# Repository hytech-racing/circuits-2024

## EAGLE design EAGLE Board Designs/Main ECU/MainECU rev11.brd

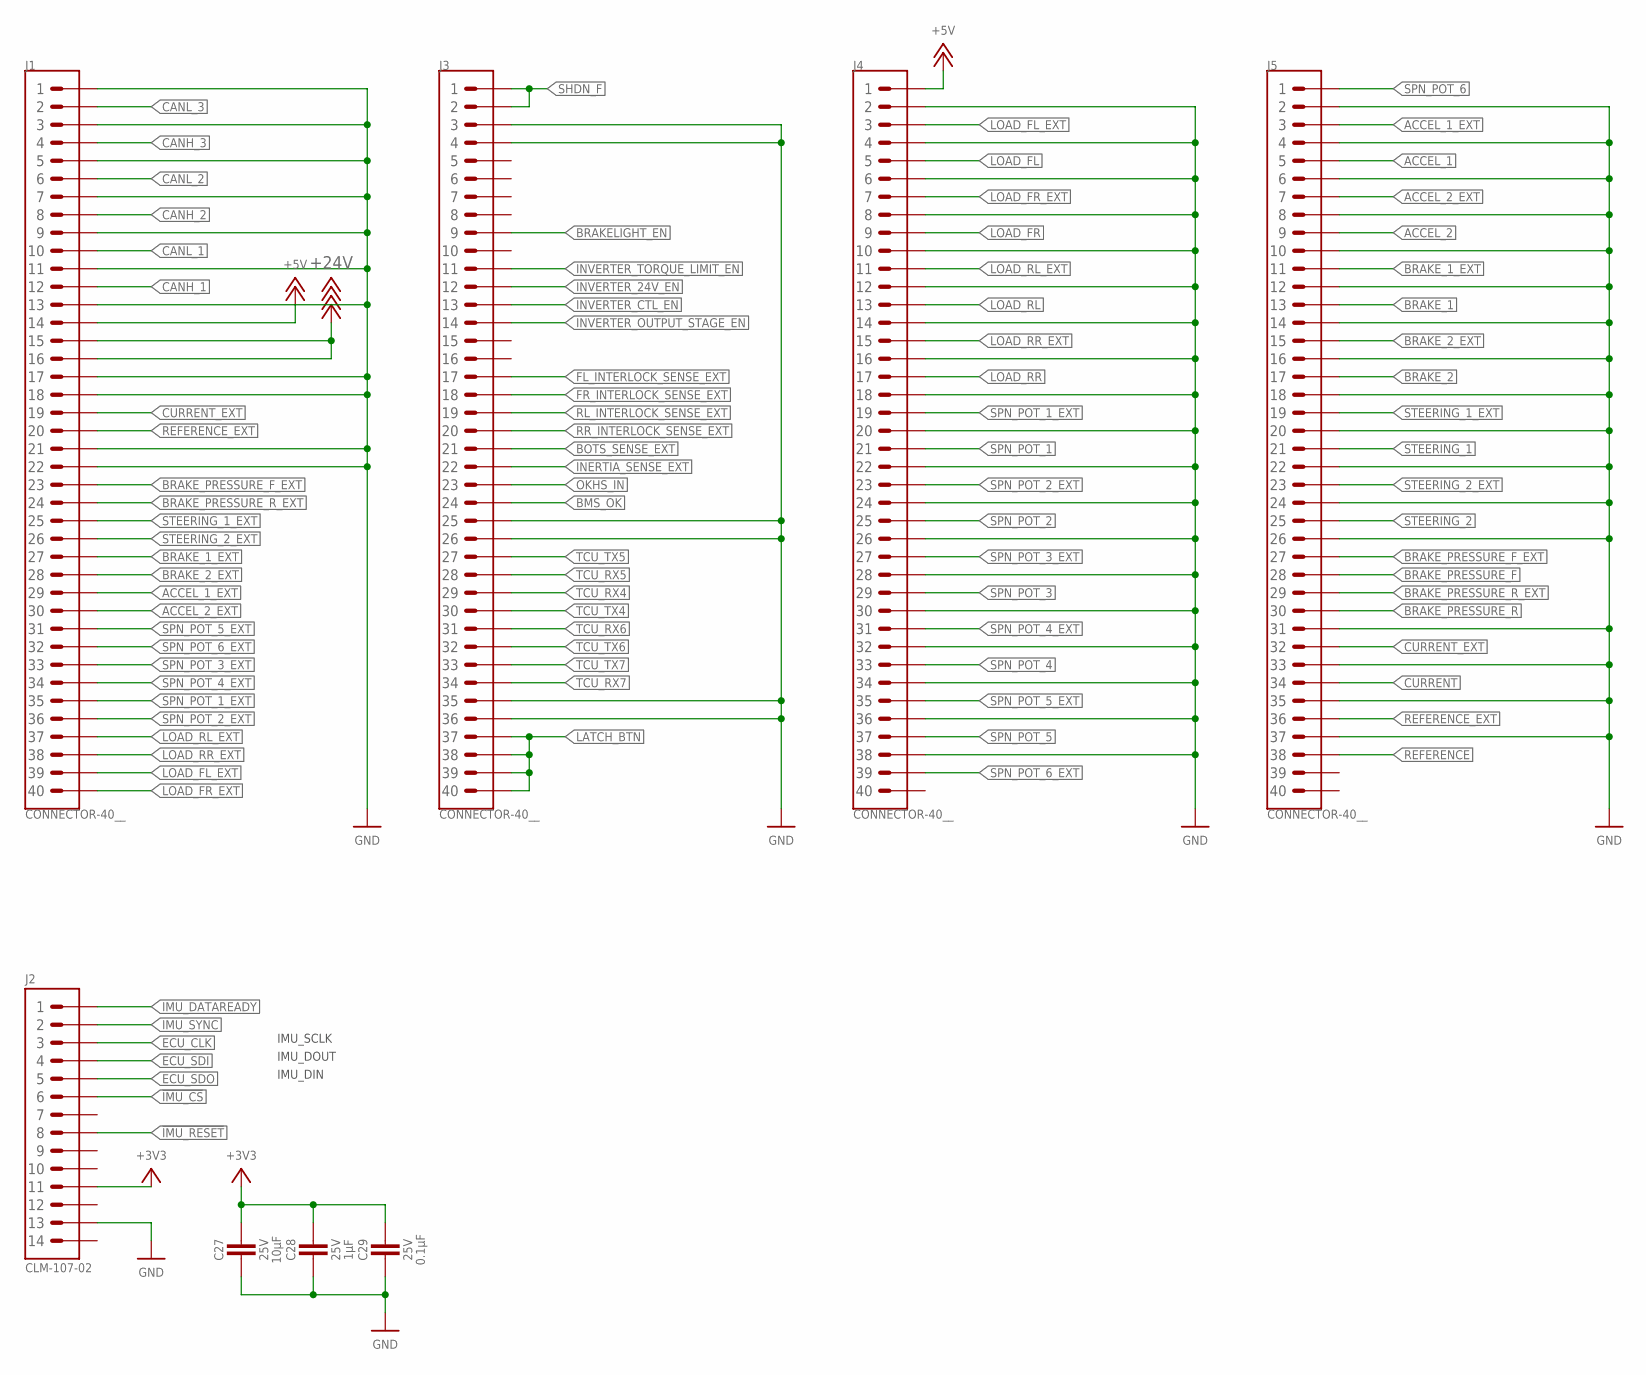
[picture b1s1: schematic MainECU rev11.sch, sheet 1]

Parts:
C27: CAPACITOR_0603_25V_10UF; 0603-CAP
C28: CAPACITOR_0603_25V_1UF; 0603-CAP
C29: CAPACITOR_0603_25V_0.1UF; 0603-CAP
J1, J3, J4, J5: CONNECTOR-40__; EHT-120-01
J2: ADIS16460

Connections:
!IMU_CS: J2.6; also elsewhere on the board
!IMU_RESET: J2.8; also elsewhere on the board
+3V3: C27.1, C28.1, C29.1, J2.11; also elsewhere on the board
+5V: J1.14, J4.1; also elsewhere on the board
+24V: J1.15, J1.16; also elsewhere on the board
ACCEL_1: J5.5; also elsewhere on the board
ACCEL_1_EXT: J1.29, J5.3
ACCEL_2: J5.9; also elsewhere on the board
ACCEL_2_EXT: J1.30, J5.7
BMS_OK: J3.24; also elsewhere on the board
BOTS_SENSE_EXT: J3.21; also elsewhere on the board
BRAKELIGHT_EN: J3.9; also elsewhere on the board
BRAKE_1: J5.13; also elsewhere on the board
BRAKE_1_EXT: J1.27, J5.11
BRAKE_2: J5.17; also elsewhere on the board
BRAKE_2_EXT: J1.28, J5.15
BRAKE_PRESSURE_F: J5.28; also elsewhere on the board
BRAKE_PRESSURE_F_EXT: J1.23, J5.27
BRAKE_PRESSURE_R: J5.30; also elsewhere on the board
BRAKE_PRESSURE_R_EXT: J1.24, J5.29
CANH_1: J1.12; also elsewhere on the board
CANH_2: J1.8; also elsewhere on the board
CANH_3: J1.4; also elsewhere on the board
CANL_1: J1.10; also elsewhere on the board
CANL_2: J1.6; also elsewhere on the board
CANL_3: J1.2; also elsewhere on the board
CURRENT: J5.34; also elsewhere on the board
CURRENT_EXT: J1.19, J5.32
ECU_CLK: J2.3; also elsewhere on the board
ECU_SDI: J2.4; also elsewhere on the board
ECU_SDO: J2.5; also elsewhere on the board
FL_INTERLOCK_SENSE_EXT: J3.17; also elsewhere on the board
FR_INTERLOCK_SENSE_EXT: J3.18; also elsewhere on the board
GND: C27.2, C28.2, C29.2, J1.1, J1.3, J1.5, J1.7, J1.9, J1.11, J1.13, J1.17, J1.18, J1.21, J1.22, J2.13, J3.3, J3.4, J3.25, J3.26, J3.35, J3.36, J4.2, J4.4, J4.6, J4.8, J4.10, J4.12, J4.14, J4.16, J4.18, J4.20, J4.22, J4.24, J4.26, J4.28, J4.30, J4.32, J4.34, J4.36, J4.38, J5.2, J5.4, J5.6, J5.8, J5.10, J5.12, J5.14, J5.16, J5.18, J5.20, J5.22, J5.24, J5.26, J5.31, J5.33, J5.35, J5.37; also elsewhere on the board
IMU_DATAREADY: J2.1; also elsewhere on the board
IMU_SYNC: J2.2; also elsewhere on the board
INERTIA_SENSE_EXT: J3.22; also elsewhere on the board
INVERTER_24V_EN: J3.12; also elsewhere on the board
INVERTER_CTL_EN: J3.13; also elsewhere on the board
INVERTER_OUTPUT_STAGE_EN: J3.14; also elsewhere on the board
INVERTER_TORQUE_LIMIT_EN: J3.11; also elsewhere on the board
LATCH_BTN: J3.37, J3.38, J3.39, J3.40; also elsewhere on the board
LOAD_FL: J4.5; also elsewhere on the board
LOAD_FL_EXT: J1.39, J4.3
LOAD_FR: J4.9; also elsewhere on the board
LOAD_FR_EXT: J1.40, J4.7
LOAD_RL: J4.13; also elsewhere on the board
LOAD_RL_EXT: J1.37, J4.11
LOAD_RR: J4.17; also elsewhere on the board
LOAD_RR_EXT: J1.38, J4.15
OKHS_IN: J3.23; also elsewhere on the board
REFERENCE: J5.38; also elsewhere on the board
REFERENCE_EXT: J1.20, J5.36
RL_INTERLOCK_SENSE_EXT: J3.19; also elsewhere on the board
RR_INTERLOCK_SENSE_EXT: J3.20; also elsewhere on the board
SHDN_F: J3.1, J3.2; also elsewhere on the board
SPN_POT_1: J4.21; also elsewhere on the board
SPN_POT_1_EXT: J1.35, J4.19
SPN_POT_2: J4.25; also elsewhere on the board
SPN_POT_2_EXT: J1.36, J4.23
SPN_POT_3: J4.29; also elsewhere on the board
SPN_POT_3_EXT: J1.33, J4.27
SPN_POT_4: J4.33; also elsewhere on the board
SPN_POT_4_EXT: J1.34, J4.31
SPN_POT_5: J4.37; also elsewhere on the board
SPN_POT_5_EXT: J1.31, J4.35
SPN_POT_6: J5.1; also elsewhere on the board
SPN_POT_6_EXT: J1.32, J4.39
STEERING_1: J5.21; also elsewhere on the board
STEERING_1_EXT: J1.25, J5.19
STEERING_2: J5.25; also elsewhere on the board
STEERING_2_EXT: J1.26, J5.23
TCU_RX4: J3.29; also elsewhere on the board
TCU_RX5: J3.28; also elsewhere on the board
TCU_RX6: J3.31; also elsewhere on the board
TCU_RX7: J3.34; also elsewhere on the board
TCU_TX4: J3.30; also elsewhere on the board
TCU_TX5: J3.27; also elsewhere on the board
TCU_TX6: J3.32; also elsewhere on the board
TCU_TX7: J3.33; also elsewhere on the board

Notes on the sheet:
IMU_DOUT
IMU_SCLK
IMU_DIN

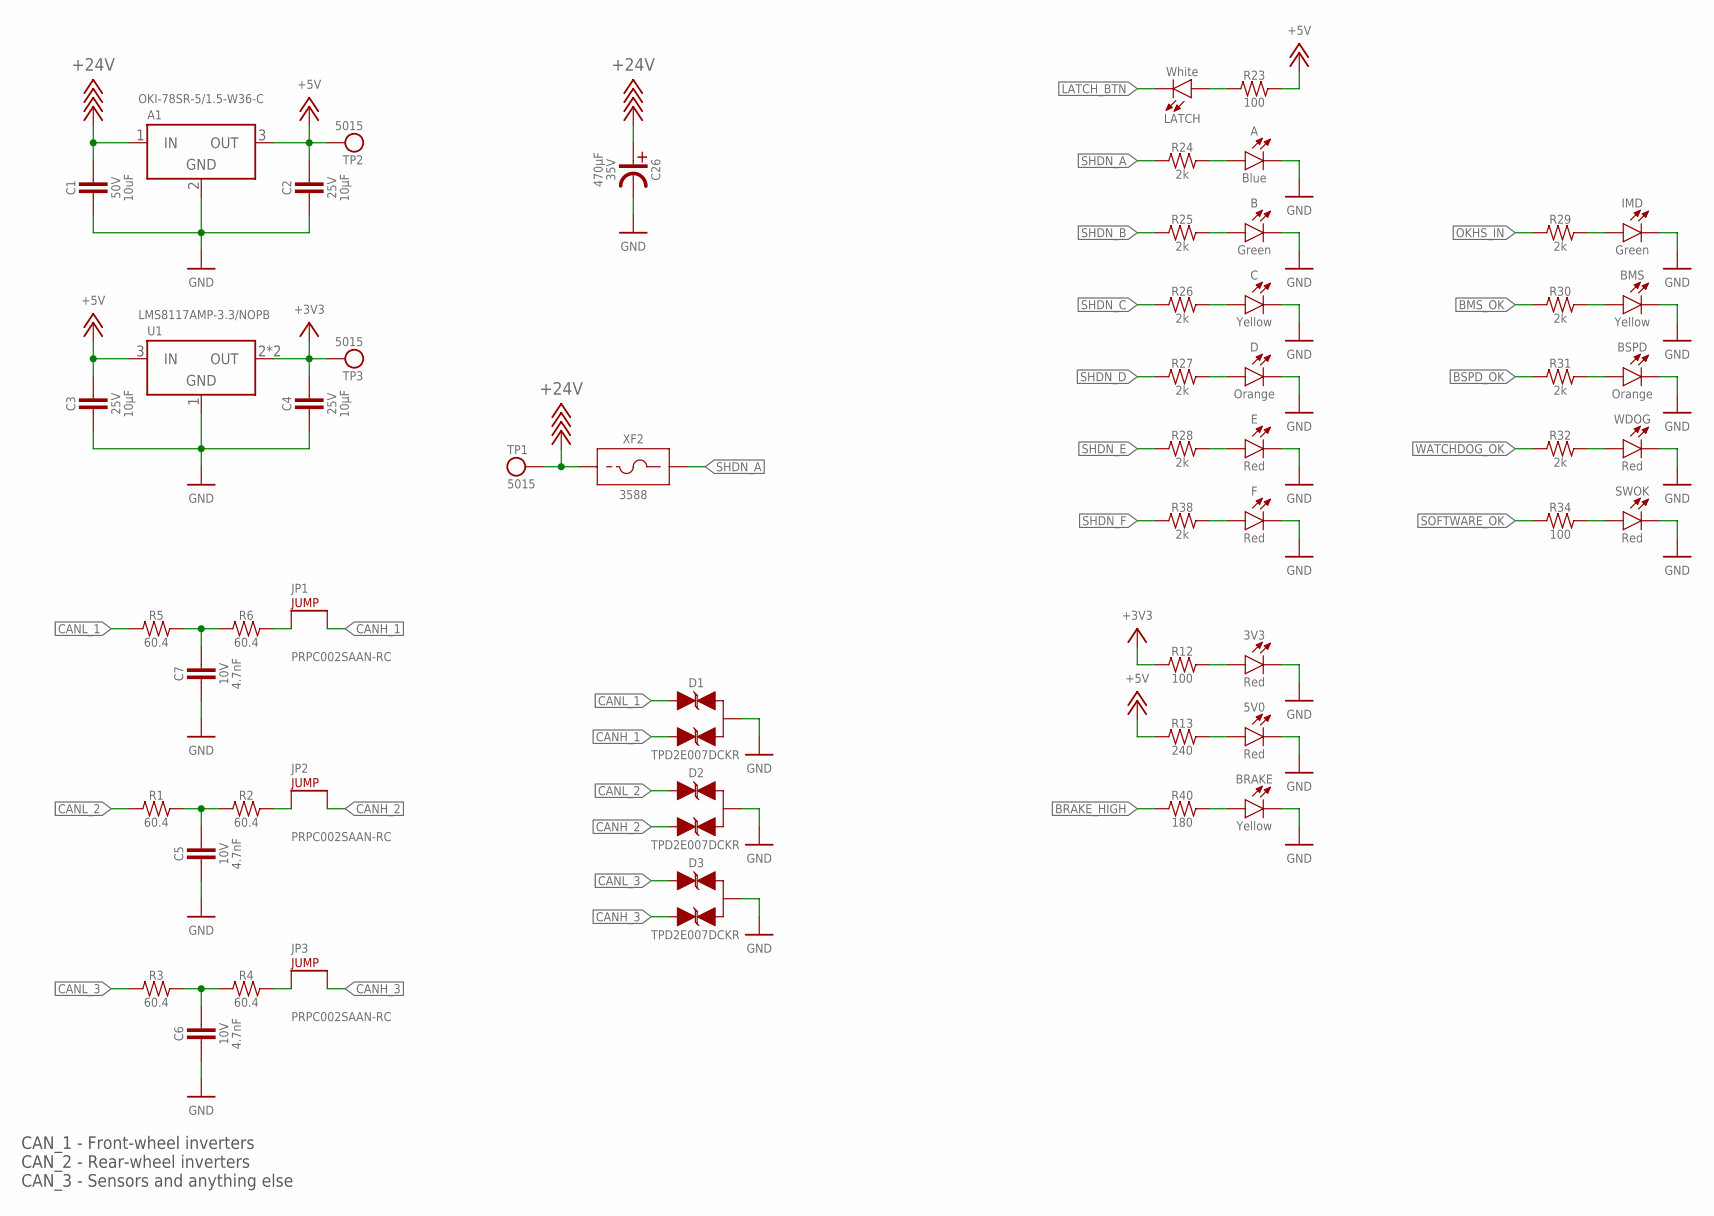
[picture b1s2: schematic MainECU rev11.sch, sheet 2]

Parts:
3V3, 5V0: LED_0603_RED; 0603-LED
A: LED_0603_BLUE; 0603-LED
A1: VOLTAGE_REGULATOR_MODULE_OKI-78SR_5V; OKI-78SR
B: LED_0603_GREEN; 0603-LED
BMS: LED_0603_YELLOW; 0603-LED
BRAKE: LED_0603_YELLOW; 0603-LED
BSPD: LED_0603_ORANGE; 0603-LED
C: LED_0603_YELLOW; 0603-LED
C1: CAPACITOR_0805_50V_10UF; 0805-CAP
C2, C3, C4: CAPACITOR_0603_25V_10UF; 0603-CAP
C5, C6, C7: CAPACITOR_0603_10V_4.7NF; 0603-CAP
C26: EEH-AZS1V471B; EEH-AZS
D: LED_0603_ORANGE; 0603-LED
D1, D2, D3: TVS_BIDIRECTIONAL_DUAL; SC-70-3
E: LED_0603_RED; 0603-LED
F: LED_0603_RED; 0603-LED
IMD: LED_0603_GREEN; 0603-LED
JP1, JP2, JP3: JUMPER__1X02; 1X02
LATCH: LED_0603_WHITE; 0603-LED
R1, R2, R3, R4, R5, R6: RESISTOR_0603_60.4; 0603-RES
R12, R23, R34: RESISTOR_0603_100; 0603-RES
R13: RESISTOR_0603_240; 0603-RES
R24, R25, R26, R27, R28, R29, R30, R31, R32, R38: RESISTOR_0603_2K; 0603-RES
R40: RESISTOR_0603_180; 0603-RES
SWOK: LED_0603_RED; 0603-LED
TP1, TP2, TP3: TEST_POINT; 5015
U1: VOLTAGE_REGULATOR_SOT-223_3.3V; SOT-223
WDOG: LED_0603_RED; 0603-LED
XF2: FUSE_HOLDER_MINIBLADESMD; 3588

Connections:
+3V3: C4.1, R12.1, TP3.1, U1.2 (OUT), U1.4 (OUT); also elsewhere on the board
+5V: A1.3 (OUT), C2.1, C3.1, R13.1, R23.2, TP2.1, U1.3 (IN); also elsewhere on the board
+24V: A1.1 (IN), C1.1, C26.PLUS, TP1.1, XF2.1, XF2.2 (1); also elsewhere on the board
BMS_OK: R30.1; also elsewhere on the board
BRAKE_HIGH: R40.1; also elsewhere on the board
BSPD_OK: R31.1; also elsewhere on the board
CANH_1: D1.2 (C2), JP1.2; also elsewhere on the board
CANH_2: D2.2 (C2), JP2.2; also elsewhere on the board
CANH_3: D3.2 (C2), JP3.2; also elsewhere on the board
CANL_1: D1.1 (C1), R5.1; also elsewhere on the board
CANL_2: D2.1 (C1), R1.1; also elsewhere on the board
CANL_3: D3.1 (C1), R3.1; also elsewhere on the board
GND: 3V3.1 (C), 5V0.1 (C), A.1 (C), A1.2 (GND), B.1 (C), BMS.1 (C), BRAKE.1 (C), BSPD.1 (C), C.1 (C), C1.2, C2.2, C3.2, C4.2, C5.2, C6.2, C7.2, C26.MINUS, D.1 (C), D1.3 (A), D2.3 (A), D3.3 (A), E.1 (C), F.1 (C), IMD.1 (C), SWOK.1 (C), U1.1 (GND), WDOG.1 (C); also elsewhere on the board
LATCH_BTN: LATCH.1 (C); also elsewhere on the board
unnamed: JP1.1, R6.2
unnamed: JP2.1, R2.2
unnamed: JP3.1, R4.2
unnamed: C5.1, R1.2, R2.1
unnamed: C6.1, R3.2, R4.1
unnamed: C7.1, R5.2, R6.1
unnamed: F.2 (A), R38.2
unnamed: LATCH.2 (A), R23.1
unnamed: A.2 (A), R24.2
unnamed: B.2 (A), R25.2
unnamed: C.2 (A), R26.2
unnamed: D.2 (A), R27.2
unnamed: E.2 (A), R28.2
unnamed: IMD.2 (A), R29.2
unnamed: BMS.2 (A), R30.2
unnamed: BSPD.2 (A), R31.2
unnamed: R32.2, WDOG.2 (A)
unnamed: 3V3.2 (A), R12.2
unnamed: R34.2, SWOK.2 (A)
unnamed: 5V0.2 (A), R13.2
unnamed: BRAKE.2 (A), R40.2
OKHS_IN: R29.1; also elsewhere on the board
SHDN_A: R24.1, XF2.3 (2), XF2.4 (2); also elsewhere on the board
SHDN_B: R25.1; also elsewhere on the board
SHDN_C: R26.1; also elsewhere on the board
SHDN_D: R27.1; also elsewhere on the board
SHDN_E: R28.1; also elsewhere on the board
SHDN_F: R38.1; also elsewhere on the board
SOFTWARE_OK: R34.1; also elsewhere on the board
WATCHDOG_OK: R32.1; also elsewhere on the board

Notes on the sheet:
CAN_1 - Front-wheel inverters CAN_2 - Rear-wheel inverters CAN_3 - Sensors and anything else

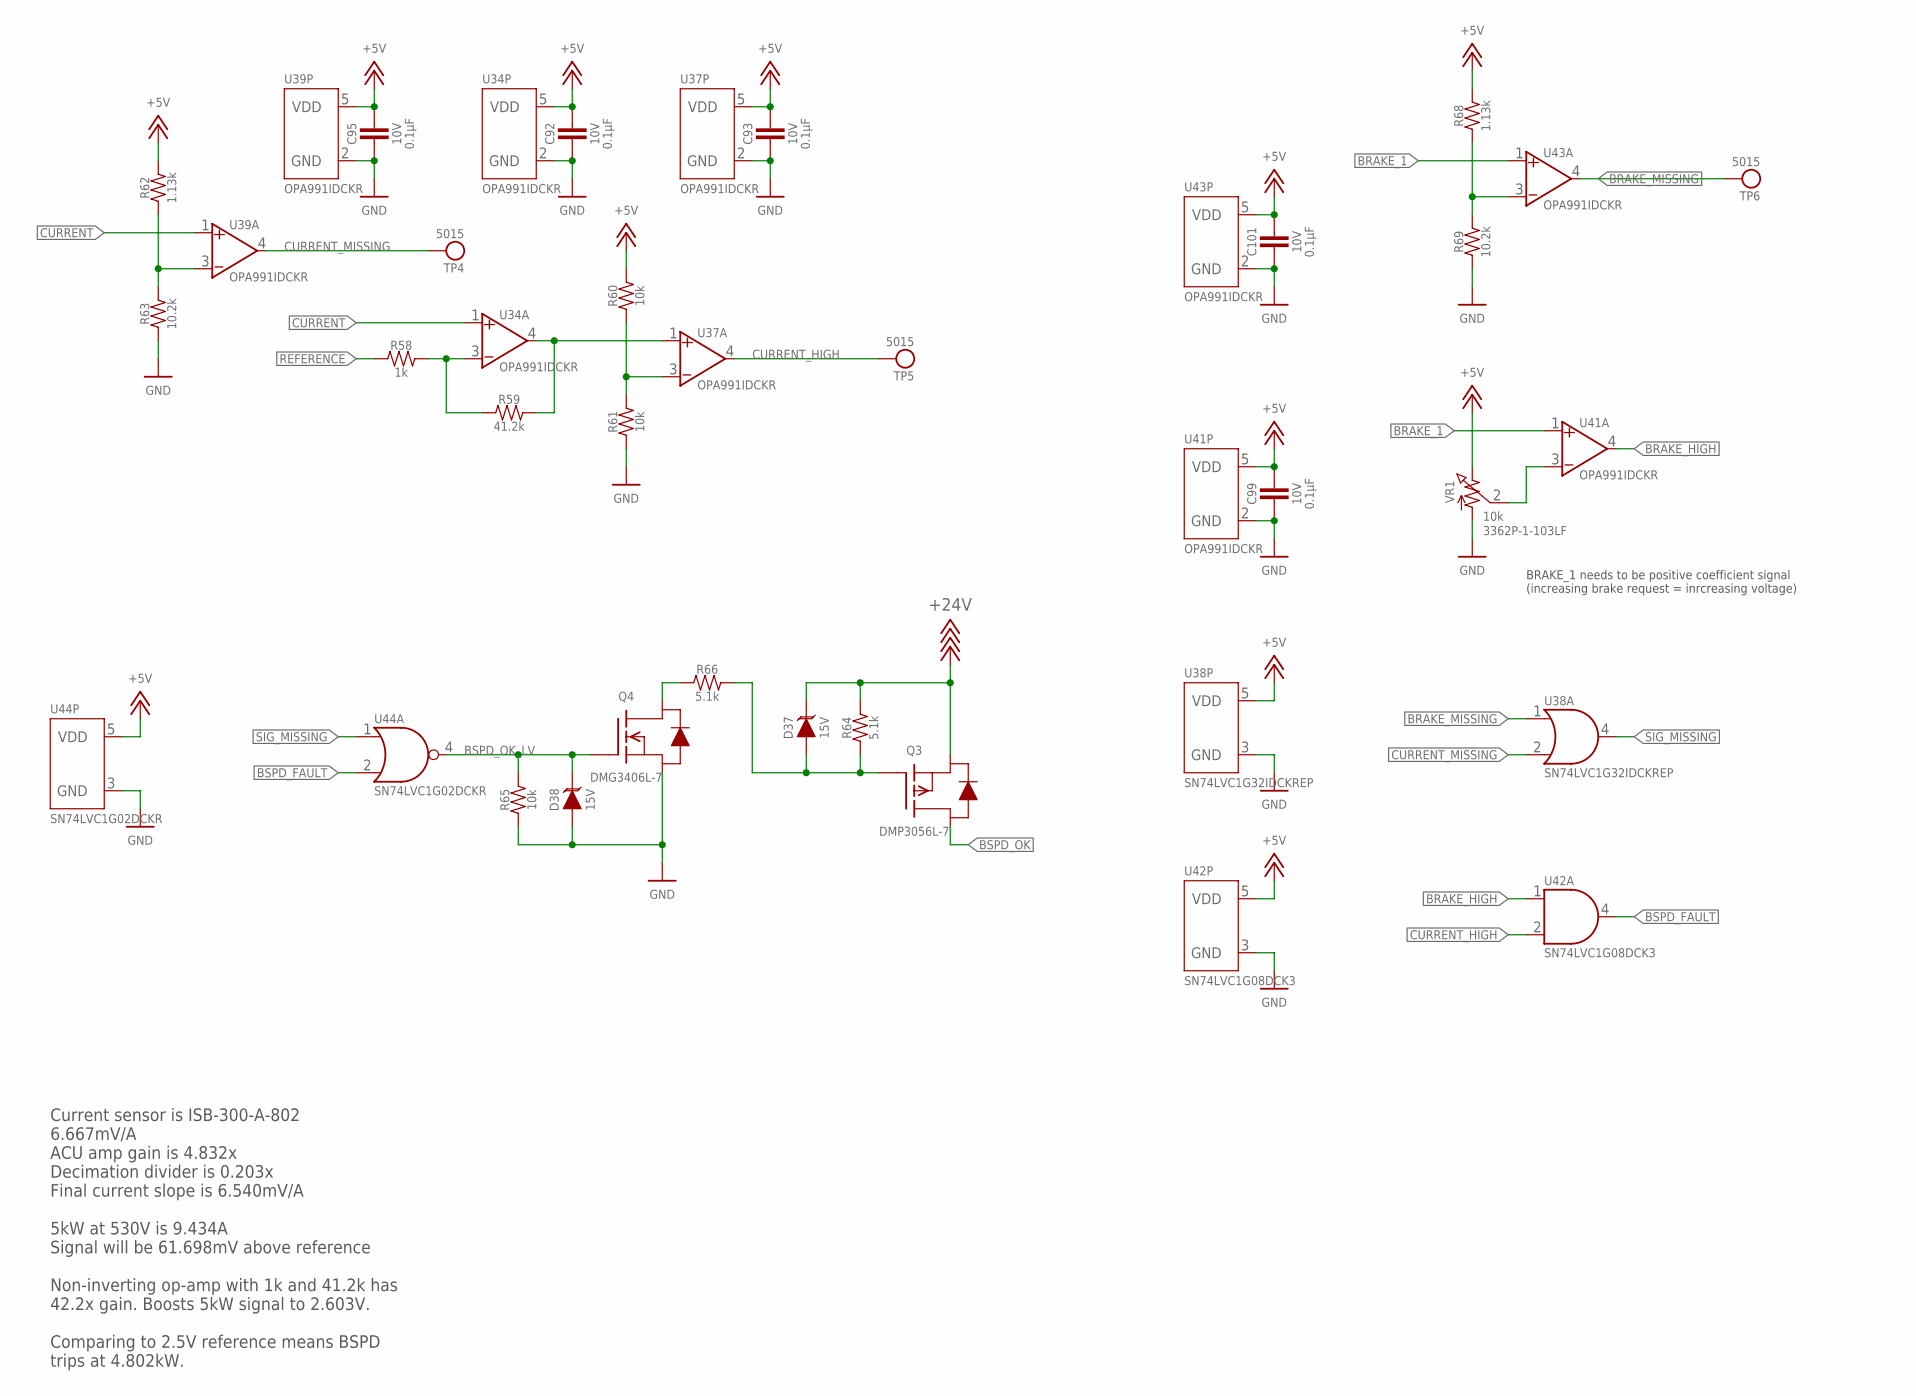
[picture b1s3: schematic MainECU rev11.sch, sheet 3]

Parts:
C92, C93, C95, C99, C101: CAPACITOR_0603_10V_0.1UF; 0603-CAP
D37, D38: TVS_15V; SOT-23
Q3: TRANSISTOR_P_MOS_SOT-23_DMP3056L-7; SOT-23
Q4: TRANSISTOR_N_MOS__DMG3406L-7; SOT-23
R58: RESISTOR_0603_1K; 0603-RES
R59: RESISTOR_0603_41.2K; 0603-RES
R60, R61, R65: RESISTOR_0603_10K; 0603-RES
R62, R68: RESISTOR_0603_1.13K; 0603-RES
R63, R69: RESISTOR_0603_10.2K; 0603-RES
R64, R66: RESISTOR_0603_5.1K; 0603-RES
TP4, TP5, TP6: TEST_POINT; 5015
U34, U37, U39, U41, U43: OPAMP_1_CHANNEL_OPA991; SC-70-5
U38: LOGICGATE_OR; SC-70-5
U42: LOGICGATE_AND_DCK3; SC-70-5
U44: LOGICGATE_NOR; SC-70-5
VR1: RESISTOR_TRIMPOT_10K_3362P; 3362P

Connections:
+5V: C92.1, C93.1, C95.1, C99.1, C101.1, R60.2, R62.2, R68.2, U34.5 (VDD), U37.5 (VDD), U38.5 (VDD), U39.5 (VDD), U41.5 (VDD), U42.5 (VDD), U43.5 (VDD), U44.5 (VDD), VR1.3 (2); also elsewhere on the board
+24V: D37.3 (C), Q3.2 (S), R64.2; also elsewhere on the board
BRAKE_1: U41.1 (VIN+), U43.1 (VIN+); also elsewhere on the board
BRAKE_HIGH: U41.4 (VOUT), U42.1 (IN1); also elsewhere on the board
BRAKE_MISSING: TP6.1, U38.1 (IN1), U43.4 (VOUT)
BSPD_FAULT: U42.4 (OUT), U44.2 (IN2)
BSPD_OK: Q3.3 (D); also elsewhere on the board
BSPD_OK_LV: D38.3 (C), Q4.1 (G), R65.2, U44.4 (OUT)
CURRENT: U34.1 (VIN+), U39.1 (VIN+); also elsewhere on the board
CURRENT_HIGH: TP5.1, U37.4 (VOUT), U42.2 (IN2)
CURRENT_MISSING: TP4.1, U38.2 (IN2), U39.4 (VOUT)
GND: C92.2, C93.2, C95.2, C99.2, C101.2, D38.1 (A), Q4.2 (S), R61.1, R63.1, R65.1, R69.1, U34.2 (GND), U37.2 (GND), U38.3 (GND), U39.2 (GND), U41.2 (GND), U42.3 (GND), U43.2 (GND), U44.3 (GND), VR1.1; also elsewhere on the board
unnamed: R60.1, R61.2, U37.3 (VIN-)
unnamed: R58.2, R59.1, U34.3 (VIN-)
unnamed: R59.2, U34.4 (VOUT), U37.1 (VIN+)
unnamed: R62.1, R63.2, U39.3 (VIN-)
unnamed: U41.3 (VIN-), VR1.2 (3)
unnamed: D37.1 (A), Q3.1 (G), R64.1, R66.2
unnamed: Q4.3 (D), R66.1
unnamed: R68.1, R69.2, U43.3 (VIN-)
REFERENCE: R58.1; also elsewhere on the board
SIG_MISSING: U38.4 (OUT), U44.1 (IN1)

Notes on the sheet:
Current sensor is ISB-300-A-802 6.667mV/A ACU amp gain is 4.832x Decimation divider is 0.203x Final current slope is 6.540mV/A 5kW at 530V is 9.434A Signal will be 61.698mV above reference Non-inverting op-amp with 1k and 41.2k has 42.2x gain. Boosts 5kW signal to 2.603V. Comparing to 2.5V referenc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
BRAKE_1 needs to be positive coefficient signal (increasing brake request = inrcreasing voltage)

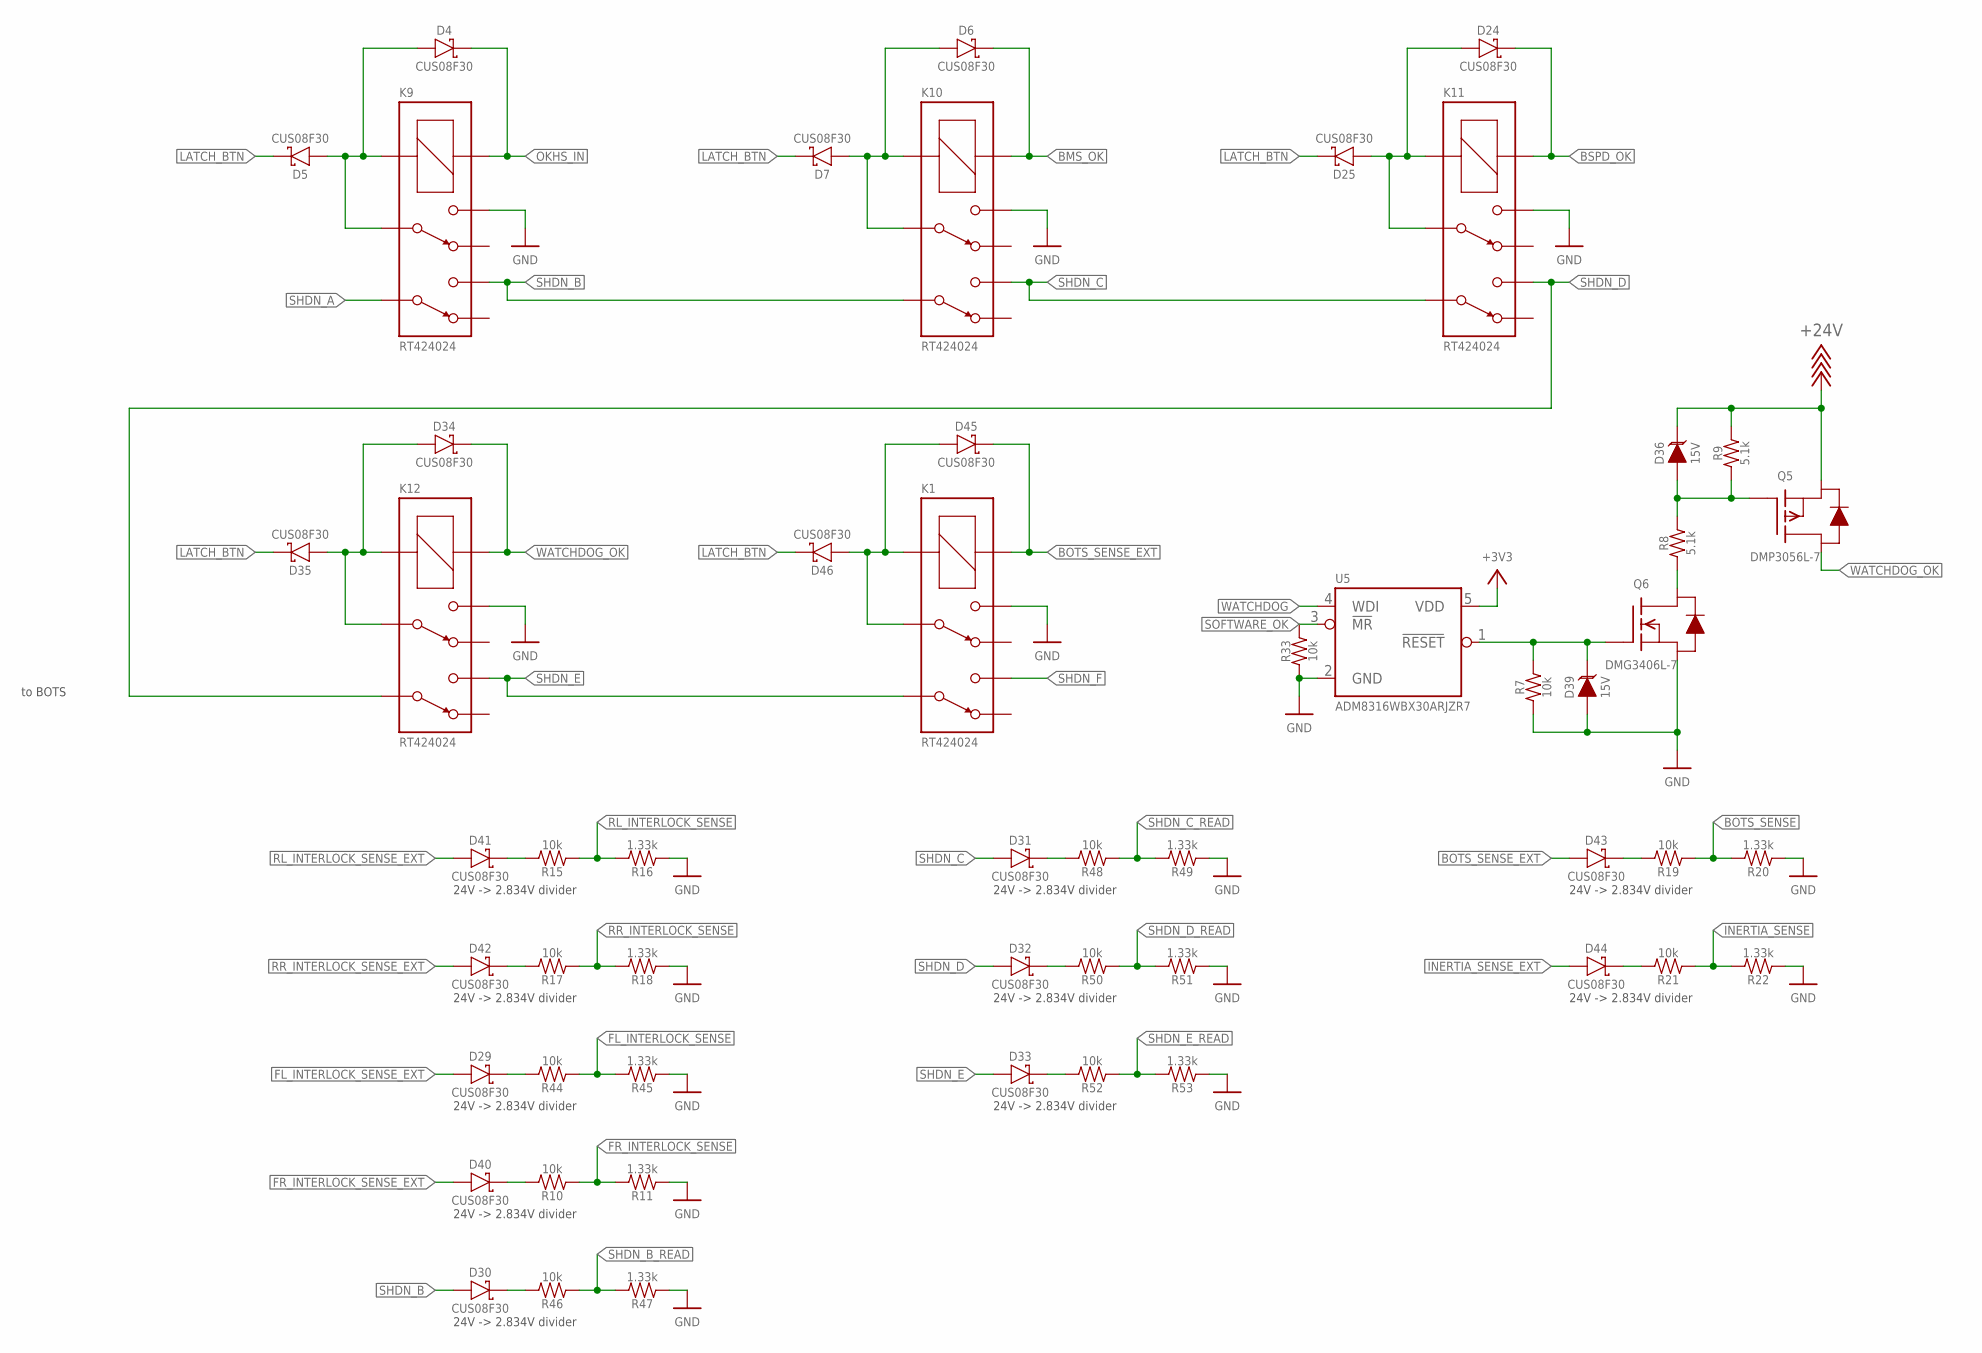
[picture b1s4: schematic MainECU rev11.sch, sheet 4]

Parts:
D4, D5, D6, D7, D24, D25, D29, D30, D31, D32, D33, D34, D35, D40, D41, D42, D43, D44, D45, D46: SCHOTTKY_SOD323_30V; SOD-323
D36, D39: TVS_15V; SOT-23
K1, K9, K10, K11, K12: RELAY_DPDT_RT424024; RT*2*
Q5: TRANSISTOR_P_MOS_SOT-23_DMP3056L-7; SOT-23
Q6: TRANSISTOR_N_MOS__DMG3406L-7; SOT-23
R7, R10, R15, R17, R19, R21, R33, R44, R46, R48, R50, R52: RESISTOR_0603_10K; 0603-RES
R8, R9: RESISTOR_0603_5.1K; 0603-RES
R11, R16, R18, R20, R22, R45, R47, R49, R51, R53: RESISTOR_0603_1.33K; 0603-RES
U5: ADM8316WBX30; SOT-23-5

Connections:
+3V3: U5.5 (VDD); also elsewhere on the board
+24V: D36.3 (C), Q5.2 (S), R9.2; also elsewhere on the board
BMS_OK: D6.C, K10.A1 (COIL+); also elsewhere on the board
BOTS_SENSE: R19.1, R20.2; also elsewhere on the board
BOTS_SENSE_EXT: D43.A, D45.C, K1.A1 (COIL+); also elsewhere on the board
BSPD_OK: D24.C, K11.A1 (COIL+); also elsewhere on the board
FL_INTERLOCK_SENSE: R44.1, R45.2; also elsewhere on the board
FL_INTERLOCK_SENSE_EXT: D29.A; also elsewhere on the board
FR_INTERLOCK_SENSE: R10.1, R11.2; also elsewhere on the board
FR_INTERLOCK_SENSE_EXT: D40.A; also elsewhere on the board
GND: D39.1 (A), K1.14 (4), K9.14 (4), K10.14 (4), K11.14 (4), K12.14 (4), Q6.2 (S), R7.1, R11.1, R16.1, R18.1, R20.1, R22.1, R33.1, R45.1, R47.1, R49.1, R51.1, R53.1, U5.2 (GND); also elsewhere on the board
INERTIA_SENSE: R21.1, R22.2; also elsewhere on the board
INERTIA_SENSE_EXT: D44.A; also elsewhere on the board
LATCH_BTN: D5.C, D7.C, D25.C, D35.C, D46.C; also elsewhere on the board
unnamed: D40.C, R10.2
unnamed: D36.1 (A), Q5.1 (G), R8.2, R9.1
unnamed: Q6.3 (D), R8.1
unnamed: D41.C, R15.2
unnamed: D42.C, R17.2
unnamed: D43.C, R19.2
unnamed: D44.C, R21.2
unnamed: D4.A, D5.A, K9.11 (3), K9.A2 (COIL-)
unnamed: D24.A, D25.A, K11.11 (3), K11.A2 (COIL-)
unnamed: D6.A, D7.A, K10.11 (3), K10.A2 (COIL-)
unnamed: D45.A, D46.A, K1.11 (3), K1.A2 (COIL-)
unnamed: D34.A, D35.A, K12.11 (3), K12.A2 (COIL-)
unnamed: D29.C, R44.2
unnamed: D30.C, R46.2
unnamed: D31.C, R48.2
unnamed: D32.C, R50.2
unnamed: D33.C, R52.2
OKHS_IN: D4.C, K9.A1 (COIL+); also elsewhere on the board
RL_INTERLOCK_SENSE: R15.1, R16.2; also elsewhere on the board
RL_INTERLOCK_SENSE_EXT: D41.A; also elsewhere on the board
RR_INTERLOCK_SENSE: R17.1, R18.2; also elsewhere on the board
RR_INTERLOCK_SENSE_EXT: D42.A; also elsewhere on the board
SHDN_A: K9.21 (6); also elsewhere on the board
SHDN_B: D30.A, K9.24 (5), K10.21 (6); also elsewhere on the board
SHDN_B_READ: R46.1, R47.2; also elsewhere on the board
SHDN_C: D31.A, K10.24 (5), K11.21 (6); also elsewhere on the board
SHDN_C_READ: R48.1, R49.2; also elsewhere on the board
SHDN_D: D32.A, K11.24 (5), K12.21 (6); also elsewhere on the board
SHDN_D_READ: R50.1, R51.2; also elsewhere on the board
SHDN_E: D33.A, K1.21 (6), K12.24 (5); also elsewhere on the board
SHDN_E_READ: R52.1, R53.2; also elsewhere on the board
SHDN_F: K1.24 (5); also elsewhere on the board
SOFTWARE_OK: R33.2, U5.3 (!MR!); also elsewhere on the board
WATCHDOG: U5.4 (WDI); also elsewhere on the board
WATCHDOG_OK: D34.C, K12.A1 (COIL+), Q5.3 (D); also elsewhere on the board
WATCHDOG_OK_LV: D39.3 (C), Q6.1 (G), R7.2, U5.1 (!RESET!)

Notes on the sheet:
to BOTS
24V -> 2.834V divider

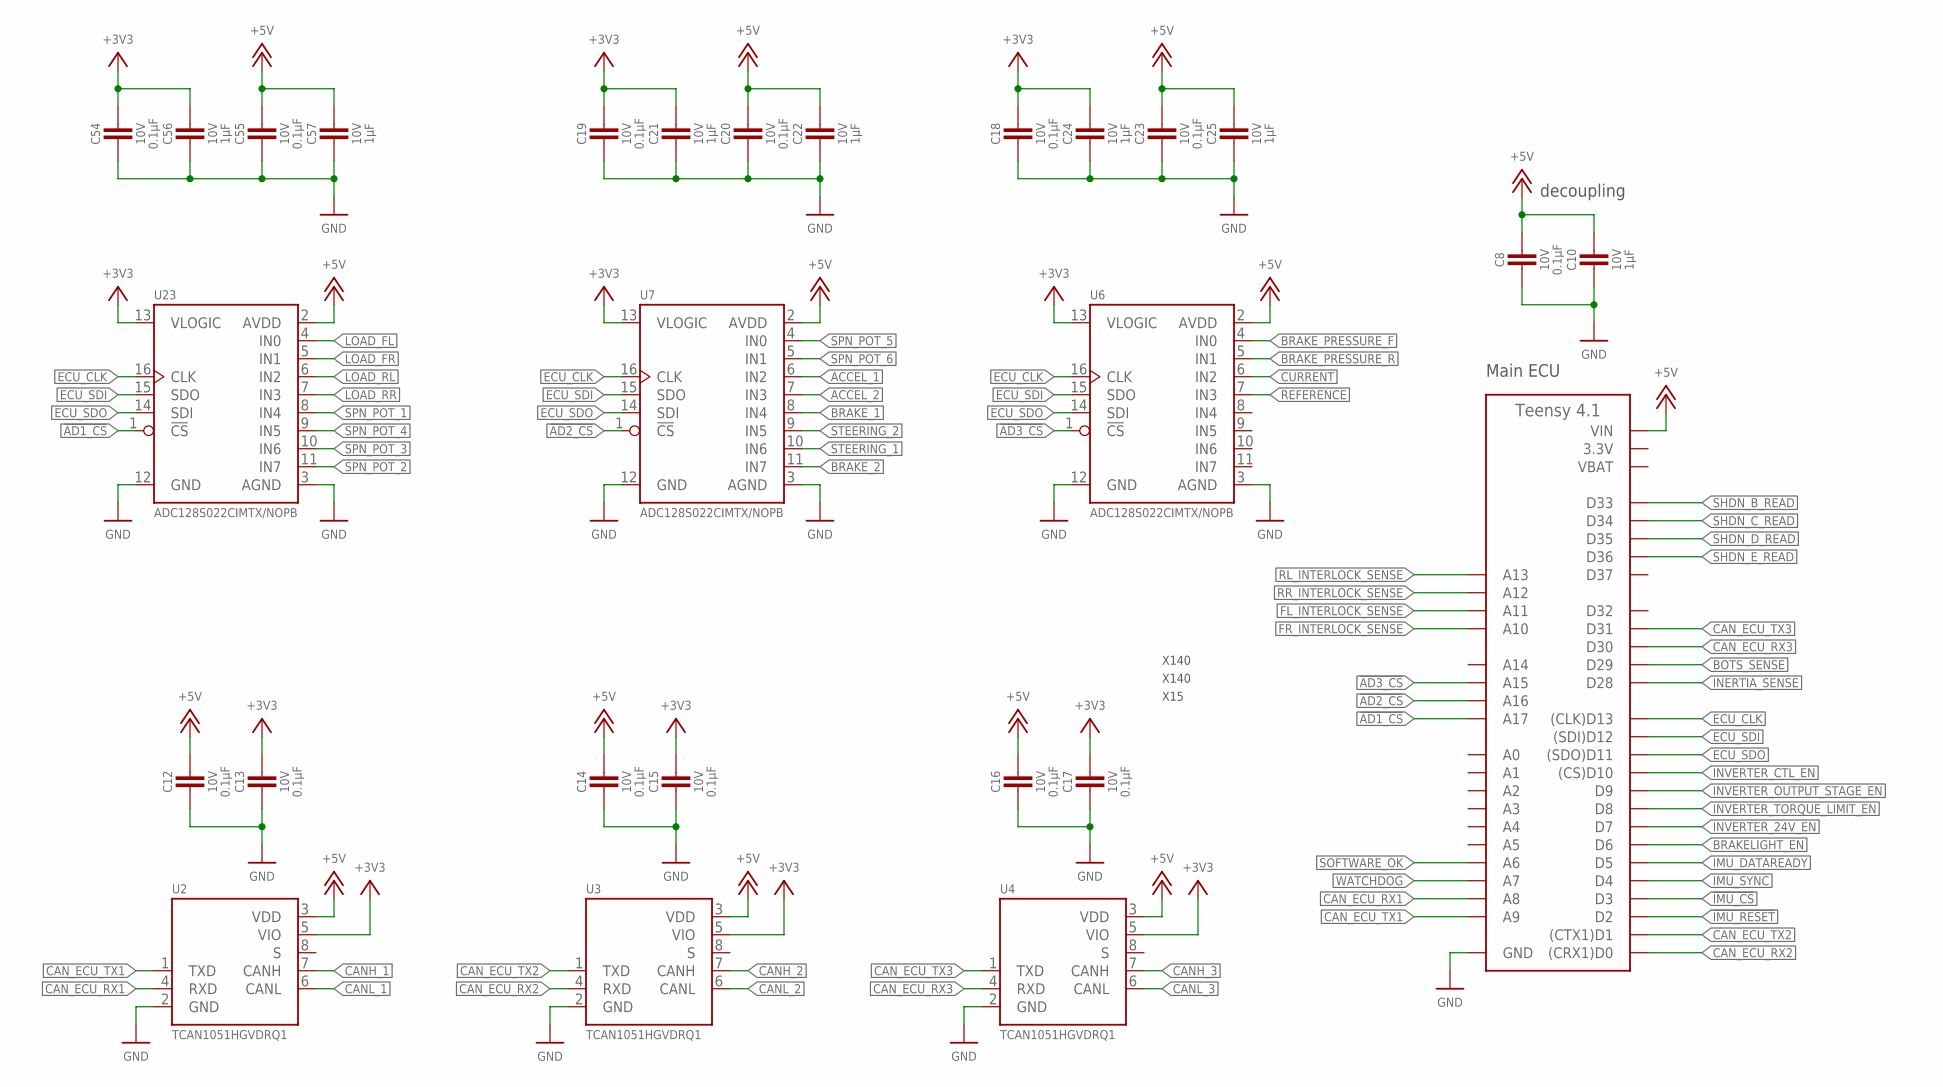
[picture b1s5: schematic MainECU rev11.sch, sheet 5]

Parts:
A2: TEENSY_4.1; TEENSY_LONG_EXT
C8, C12, C13, C14, C15, C16, C17, C18, C19, C20, C23, C54, C55: CAPACITOR_0603_10V_0.1UF; 0603-CAP
C10, C21, C22, C24, C25, C56, C57: CAPACITOR_0603_10V_1UF; 0603-CAP
U2, U3, U4: TCAN1051HQV-Q1; SOIC-08(NARROW,0.15")
U6, U7, U23: ADC128S022; TSSOP-16

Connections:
3.3V: A2.3V3 (3.3V), A2.3V3@2 (3.3V), A2.3V3@3 (3.3V); also elsewhere on the board
!AD1_CS: A2.D41 (A17), U23.1 (!CS!)
!AD2_CS: A2.D40 (A16), U7.1 (!CS!)
!AD3_CS: A2.D39 (A15), U6.1 (!CS!)
!IMU_CS: A2.D3; also elsewhere on the board
!IMU_RESET: A2.D2; also elsewhere on the board
+3V3: C13.1, C15.1, C17.1, C18.1, C19.1, C21.1, C24.1, C54.1, C56.1, U2.5 (VIO), U3.5 (VIO), U4.5 (VIO), U6.13 (VLOGIC), U7.13 (VLOGIC), U23.13 (VLOGIC); also elsewhere on the board
+5V: A2.VIN, C8.1, C10.1, C12.1, C14.1, C16.1, C20.1, C22.1, C23.1, C25.1, C55.1, C57.1, U2.3 (VDD), U3.3 (VDD), U4.3 (VDD), U6.2 (AVDD), U7.2 (AVDD), U23.2 (AVDD); also elsewhere on the board
ACCEL_1: U7.6 (IN2); also elsewhere on the board
ACCEL_2: U7.7 (IN3); also elsewhere on the board
BOTS_SENSE: A2.D29; also elsewhere on the board
BRAKELIGHT_EN: A2.D6; also elsewhere on the board
BRAKE_1: U7.8 (IN4); also elsewhere on the board
BRAKE_2: U7.11 (IN7); also elsewhere on the board
BRAKE_PRESSURE_F: U6.4 (IN0); also elsewhere on the board
BRAKE_PRESSURE_R: U6.5 (IN1); also elsewhere on the board
CANH_1: U2.7 (CANH); also elsewhere on the board
CANH_2: U3.7 (CANH); also elsewhere on the board
CANH_3: U4.7 (CANH); also elsewhere on the board
CANL_1: U2.6 (CANL); also elsewhere on the board
CANL_2: U3.6 (CANL); also elsewhere on the board
CANL_3: U4.6 (CANL); also elsewhere on the board
CAN_ECU_RX1: A2.D22 (A8), U2.4 (RXD)
CAN_ECU_RX2: A2.D0 ((CRX1)D0), U3.4 (RXD)
CAN_ECU_RX3: A2.D30, U4.4 (RXD)
CAN_ECU_TX1: A2.D23 (A9), U2.1 (TXD)
CAN_ECU_TX2: A2.D1 ((CTX1)D1), U3.1 (TXD)
CAN_ECU_TX3: A2.D31, U4.1 (TXD)
CURRENT: U6.6 (IN2); also elsewhere on the board
ECU_CLK: A2.D13 ((CLK)D13), U6.16 (CLK), U7.16 (CLK), U23.16 (CLK); also elsewhere on the board
ECU_SDI: A2.D12 ((SDI)D12), U6.15 (SDO), U7.15 (SDO), U23.15 (SDO); also elsewhere on the board
ECU_SDO: A2.D11 ((SDO)D11), U6.14 (SDI), U7.14 (SDI), U23.14 (SDI); also elsewhere on the board
FL_INTERLOCK_SENSE: A2.D25 (A11); also elsewhere on the board
FR_INTERLOCK_SENSE: A2.D24 (A10); also elsewhere on the board
GND: A2.AGND/GND (GND), A2.GND, A2.GND@2 (GND), C8.2, C10.2, C12.2, C13.2, C14.2, C15.2, C16.2, C17.2, C18.2, C19.2, C20.2, C21.2, C22.2, C23.2, C24.2, C25.2, C54.2, C55.2, C56.2, C57.2, U2.2 (GND), U3.2 (GND), U4.2 (GND), U6.3 (AGND), U6.12 (GND), U7.3 (AGND), U7.12 (GND), U23.3 (AGND), U23.12 (GND); also elsewhere on the board
IMU_DATAREADY: A2.D5; also elsewhere on the board
IMU_SYNC: A2.D4; also elsewhere on the board
INERTIA_SENSE: A2.D28; also elsewhere on the board
INVERTER_24V_EN: A2.D7; also elsewhere on the board
INVERTER_CTL_EN: A2.D10 ((CS)D10); also elsewhere on the board
INVERTER_OUTPUT_STAGE_EN: A2.D9; also elsewhere on the board
INVERTER_TORQUE_LIMIT_EN: A2.D8; also elsewhere on the board
LOAD_FL: U23.4 (IN0); also elsewhere on the board
LOAD_FR: U23.5 (IN1); also elsewhere on the board
LOAD_RL: U23.6 (IN2); also elsewhere on the board
LOAD_RR: U23.7 (IN3); also elsewhere on the board
REFERENCE: U6.7 (IN3); also elsewhere on the board
RL_INTERLOCK_SENSE: A2.D27 (A13); also elsewhere on the board
RR_INTERLOCK_SENSE: A2.D26 (A12); also elsewhere on the board
SHDN_B_READ: A2.D33; also elsewhere on the board
SHDN_C_READ: A2.D34; also elsewhere on the board
SHDN_D_READ: A2.D35; also elsewhere on the board
SHDN_E_READ: A2.D36; also elsewhere on the board
SOFTWARE_OK: A2.D20 (A6); also elsewhere on the board
SPN_POT_1: U23.8 (IN4); also elsewhere on the board
SPN_POT_2: U23.11 (IN7); also elsewhere on the board
SPN_POT_3: U23.10 (IN6); also elsewhere on the board
SPN_POT_4: U23.9 (IN5); also elsewhere on the board
SPN_POT_5: U7.4 (IN0); also elsewhere on the board
SPN_POT_6: U7.5 (IN1); also elsewhere on the board
STEERING_1: U7.10 (IN6); also elsewhere on the board
STEERING_2: U7.9 (IN5); also elsewhere on the board
VBAT: A2.VBAT; also elsewhere on the board
WATCHDOG: A2.D21 (A7); also elsewhere on the board

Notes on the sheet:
decoupling
Main ECU
X15
X140
